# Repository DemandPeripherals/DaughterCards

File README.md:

# Daughter Cards
Eagle sources for schematic and board layout for all
of the Demand Peripherals daughter cards.

These drawings are released under the Creative Commons
Share-Alike 3.0 Unported license.  Please see LICENSE
for the text of the license.

The white directory contain the schematics and layout
for cards with a white silkscreen and which have either
3.5 or 1.575 inches between mounting holes.  The black
directory has the same, or newer, schematics for cards
which have 40 or 90 millimeter mounting hole spacing.

<p> &nbsp; </p>

# System Architecture
The following diagram shows the major components in the Demand
Peripherals system. Major components include: daughter cards,
the FPGA card, dpdaemon, and your application. (The FPGA card
supports eight daughter cards although this diagram shows only
three.)

<p> &nbsp; </p>

**Dpdaemon** is a set of user space device drivers implemented
as plug-in modules. The daemon provides an ASCII API over TCP.
The daemon also acts as a multiplexer for packets to and from
the FPGA. The real functionality of dpdaemon is in a set of
loadable shared object libraries (plug-ins). While intended to
support the FPGA-based peripherals in a Demand Peripherals FPGA
image, you may find that dpdaemon has several features you'll
find useful for your next Linux-to-hardware project:
    Command line tools to view and set plug-in parameters
    Simple publish/subscribe mechanism for sensor data
    All commands and data are printable ASCII over TCP
    Modular plug-ins (drivers) for easy development
    No dependencies (excluding libc)
    Event-driven and C means low CPU/memory footprint
    GPLv2 License.

**DPCore** is the FPGA part of the peripherals.  DPCore has the
timing and logic needed to drive the electronics on the daughter
cards. For example, the FPGA part of the dc2 peripheral does the
timing for the H-bridges that controls two DC motors. Logic in
the FPGA implements an internal address and data bus and each
peripheral has a set of 8-bit registers which configure the
peripheral. For example, the FPGA peripheral part of dc2 has an
8-bit register that sets the mode (brake, coast, forward, or
reverse) of each motor. Other registers in dc2 set the duty
cycle of the H-bridge FETs and configure the watchdog timer.

The defining feature of the Demand Peripherals approach is
that 32 of the FPGA pins are grouped into "slots" of exactly
4 pins each.  The slots are completely interchangeable and
any FPGA peripheral can attach to any slot.  The use of
ribbon cables makes it easy to attach any daughter card to
any slot.

**Daughter cards** contain the electronic components needed.
Daughter cards, called interface cards on the web site,might
contain the sensors, H-Bridge FETs, or the headers to connect
to servo motors. Each daughter card connects to the FPGA card
over an eight-wire IDC cable connected to one slot. The cable
has power lines and four pins from the FPGA.  Daughter card
designs are released under a Creative Commons license.

<p> &nbsp; </p>
The picture below shows a typical system with a single board
computer, an FPGA card, four daughter cards, and two dpdaemon
managed USB peripherals.

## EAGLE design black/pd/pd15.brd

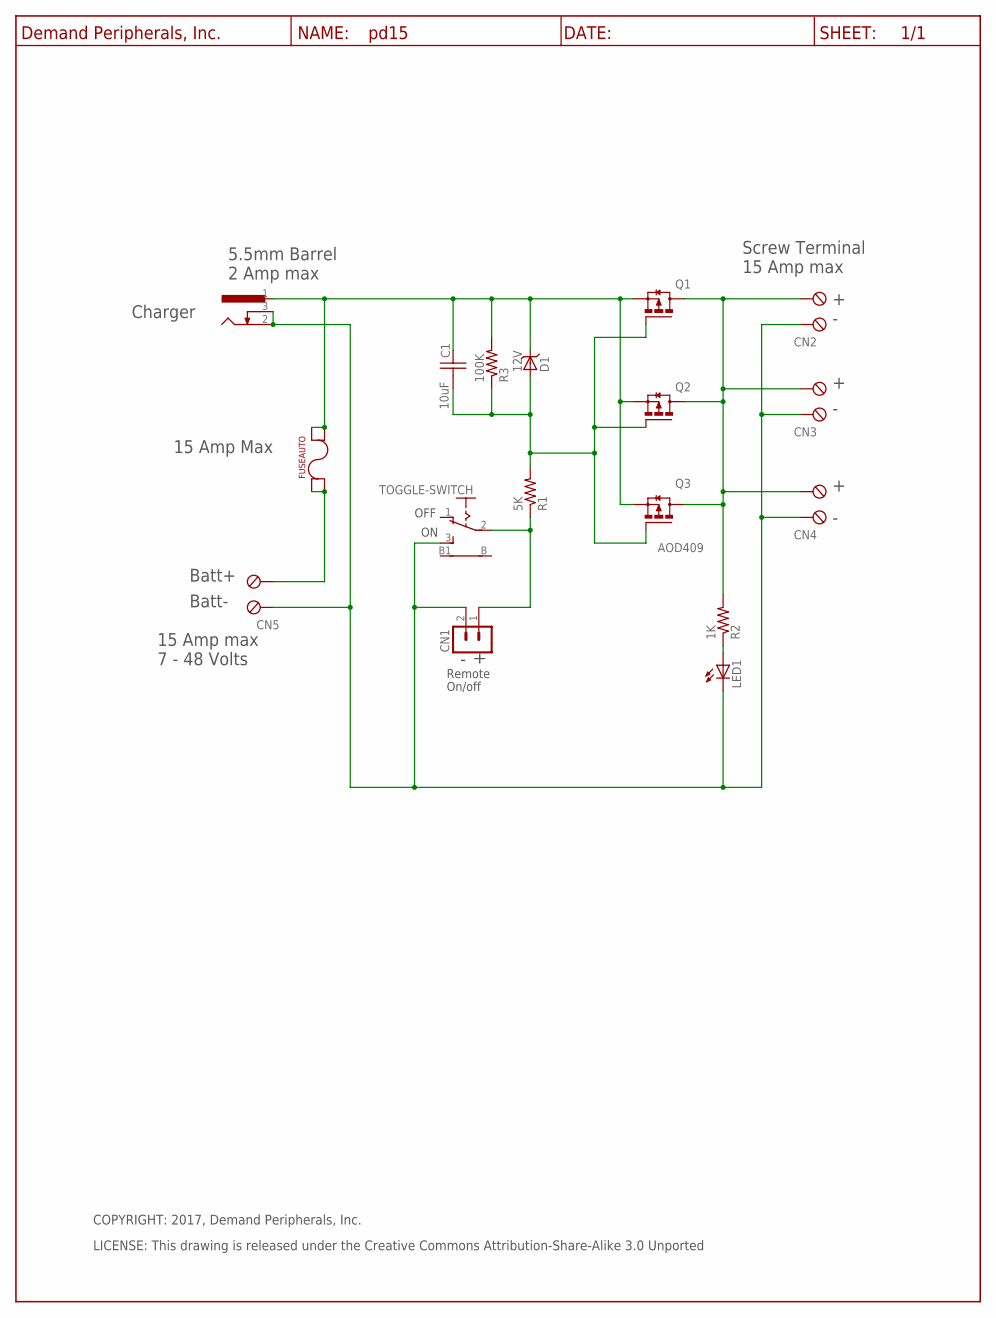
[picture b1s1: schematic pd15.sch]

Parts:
C1: 10uF; C0805
CN1: HDR-2X1-LCK; HDR-2X1
CN2, CN3, CN4, CN5: TBLK-5.08-X2
D1: 12V; SOD123
FUSE: FUSEAUTO; KS3557-10
J1: Barrel-5.5mm; DC-BARREL-JACK-55MM
LED1: LED-5MM-GRN; LED5MM
Q1, Q2: FET_DPAK_P; DPACK_TO-252
Q3: AOD409; DPACK_TO-252
R1: 5K; R0603
R2: 1K; R0603
R3: 100K; R0603
TOGGLE-SWITCH: B12EH; TOGGLE_SPDT_PC
U$1: DP_FRAME_P; LETTER_P

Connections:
BATT+: CN5.2 (KL1), FUSE.LS@1 (LS), FUSE.LS@2 (LS)
FUSE+: C1.1, D1.C, FUSE.RS@3 (RS), FUSE.RS@4 (RS), J1.1, Q1.3 (S), Q2.3 (S), Q3.3 (S), R3.2
GND: CN1.2 (1), CN2.1 (KL), CN3.1 (KL), CN4.1 (KL), CN5.1 (KL), J1.2, J1.3, LED1.C, TOGGLE-SWITCH.3 (S)
unnamed: LED1.A, R2.1
unnamed: C1.2, D1.A, Q1.1 (G), Q2.1 (G), Q3.1 (G), R1.2, R3.1
ON+: CN1.1 (2), R1.1, TOGGLE-SWITCH.2
V+: CN2.2 (KL1), CN3.2 (KL1), CN4.2 (KL1), Q1.4 (D), Q2.4 (D), Q3.4 (D), R2.2

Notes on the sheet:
Batt-
Batt+
Charger
OFF
Remote
On/off
15 Amp Max
7 - 48 Volts
15 Amp max
2 Amp max
5.5mm Barrel
Screw Terminal
COPYRIGHT: 2017, Demand Peripherals, Inc.
LICENSE: This drawing is released under the Creative Commons Attribution-Share-Alike 3.0 Unported

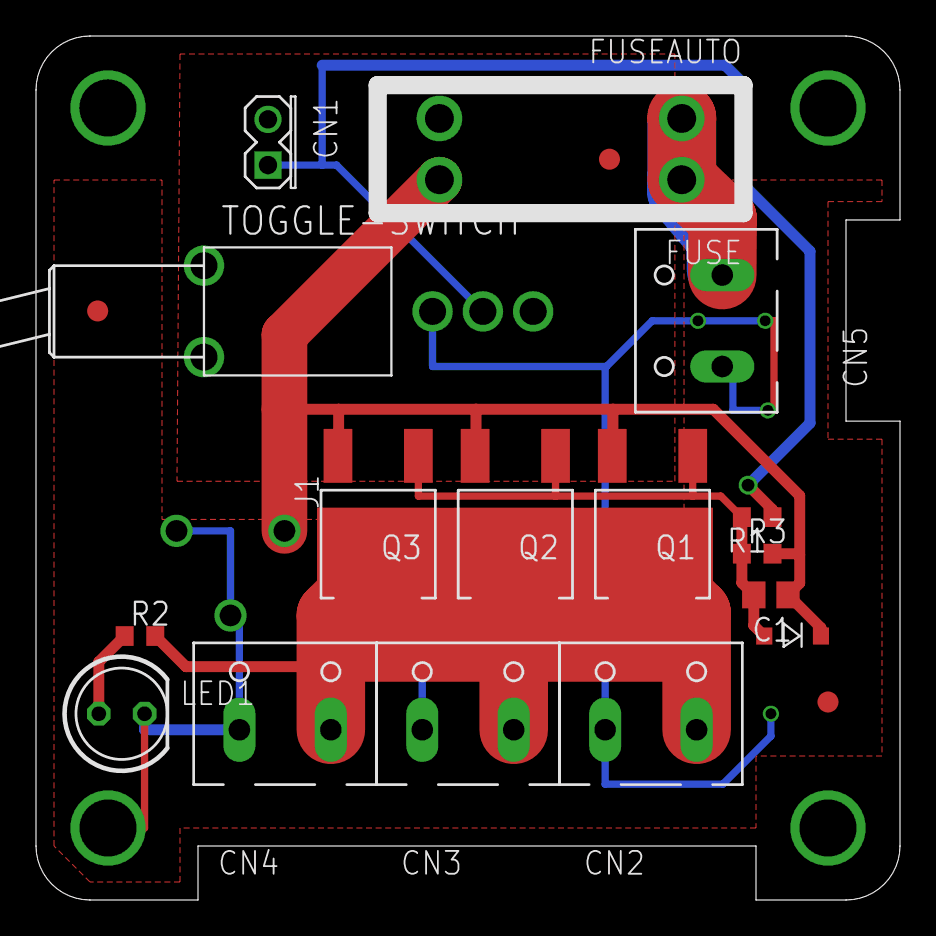
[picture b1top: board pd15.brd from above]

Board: 2 copper layers, 48.0 x 48.0 mm, 22 parts (1 on the bottom side), 7 nets.

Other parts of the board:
U$3, U$4, U$12: FIDUCIAL
U$8: DPI-2

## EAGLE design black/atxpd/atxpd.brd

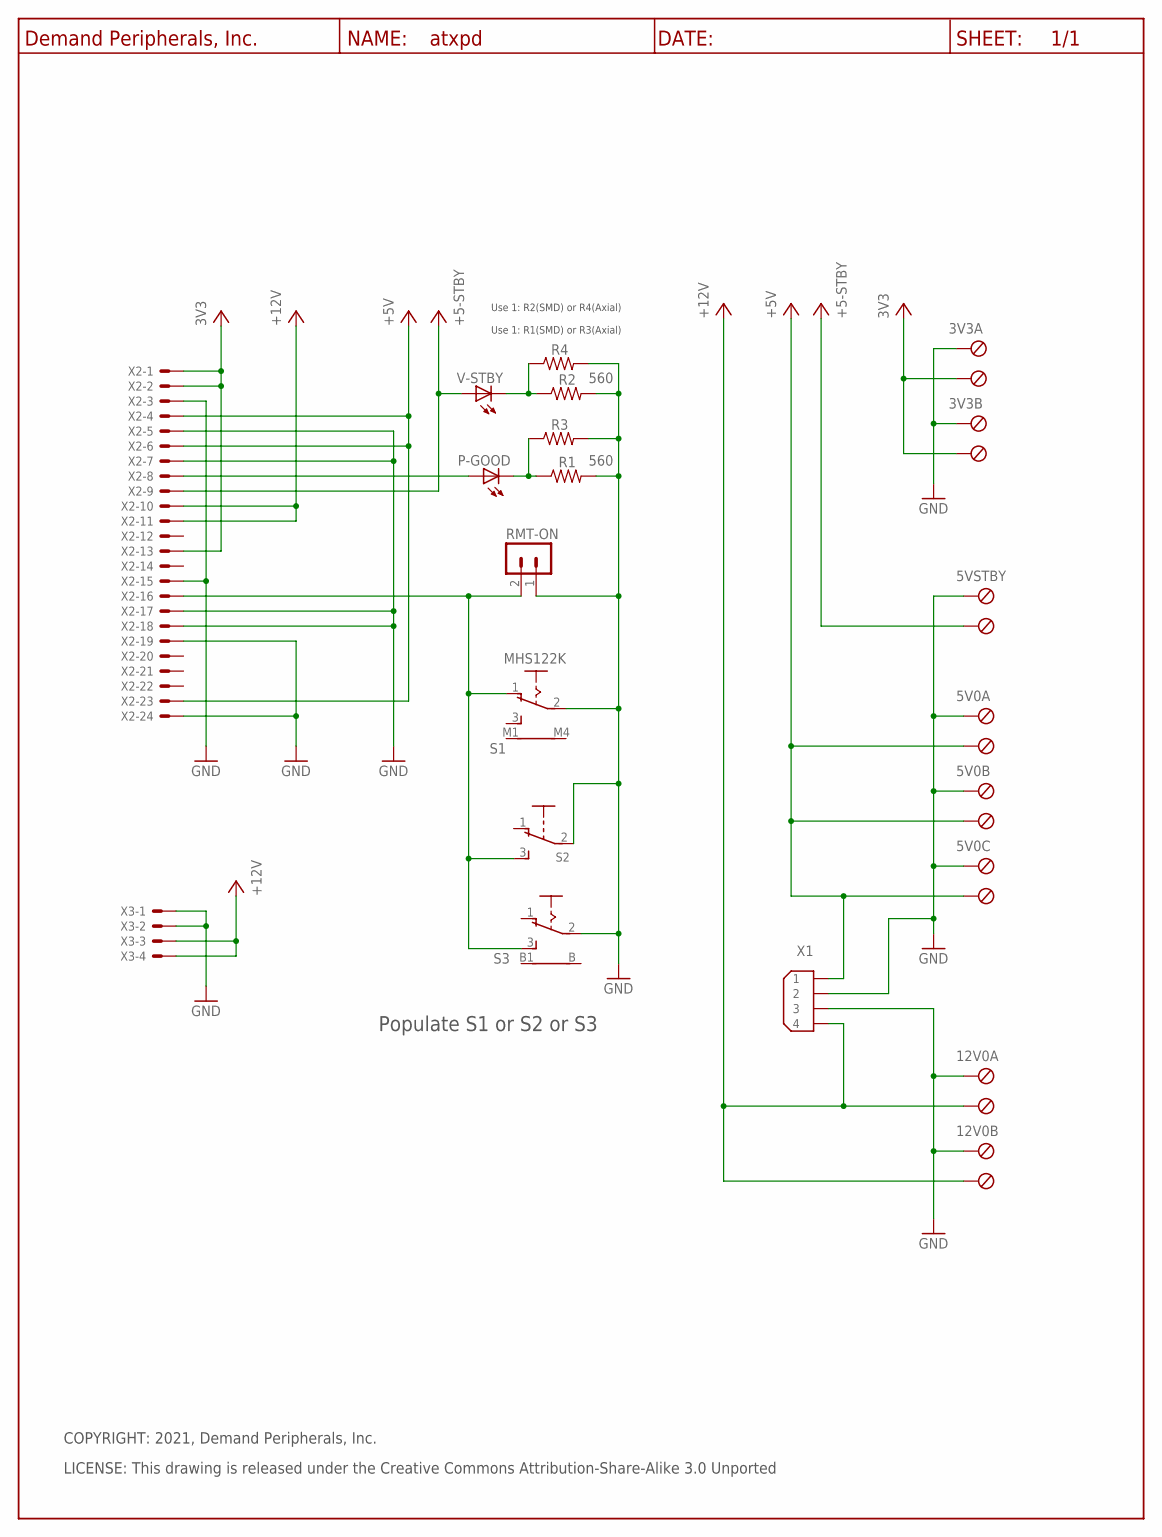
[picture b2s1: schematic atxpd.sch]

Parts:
3V3A, 3V3B, 5V0A, 5V0B, 5V0C, 5VSTBY, 12V0A, 12V0B: TBLK-5.08-X2
P-GOOD: 3mm_LED; LED5MM
R1, R2: 560; R0603
R3, R4: 560; R4TENTHS
RMT-ON: PinHdr254-2; HDR-2X1
S1: MHS122K
S2: TINYTOGGLE-SPDT-TH; SPDT-TENTHINCH
S3: Vert_SW(Option); TOGGLE_SPDT_PC
U$1: DP_FRAME_P; LETTER_P
V-STBY: 3mm_LED; LED5MM
X1: 9090-4V
X2: ATX_Std; 5566-24MOD
X3: ATX_Plus4; 5566-4MOD

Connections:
+3,3V: 3V3A.2 (KL1), 3V3B.2 (KL1), X2.1, X2.2, X2.13
+5V: 5V0A.2 (KL1), 5V0B.2 (KL1), 5V0C.2 (KL1), X1.1, X2.4, X2.6, X2.23
+5V/1: 5VSTBY.2 (KL1), V-STBY.A, X2.9
+5V/2: 12V0A.2 (KL1), 12V0B.2 (KL1), X1.4, X2.10, X2.11, X3.3, X3.4
GND: 3V3A.1 (KL), 3V3B.1 (KL), 5V0A.1 (KL), 5V0B.1 (KL), 5V0C.1 (KL), 5VSTBY.1 (KL), 12V0A.1 (KL), 12V0B.1 (KL), R1.2, R2.2, R3.2, R4.2, RMT-ON.1 (2), S1.2, S2.2, S3.2, X1.2, X1.3, X2.3, X2.5, X2.7, X2.15, X2.17, X2.18, X2.19, X2.24, X3.1, X3.2
unnamed: P-GOOD.A, X2.8
unnamed: P-GOOD.C, R1.1, R3.1
unnamed: R2.1, R4.1, V-STBY.C
unnamed: RMT-ON.2 (1), S1.1 (O), S2.3, S3.3 (S), X2.16

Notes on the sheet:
Use 1: R2(SMD) or R4(Axial)
Use 1: R1(SMD) or R3(Axial)
Populate S1 or S2 or S3
LICENSE: This drawing is released under the Creative Commons Attribution-Share-Alike 3.0 Unported
COPYRIGHT: 2021, Demand Peripherals, Inc.

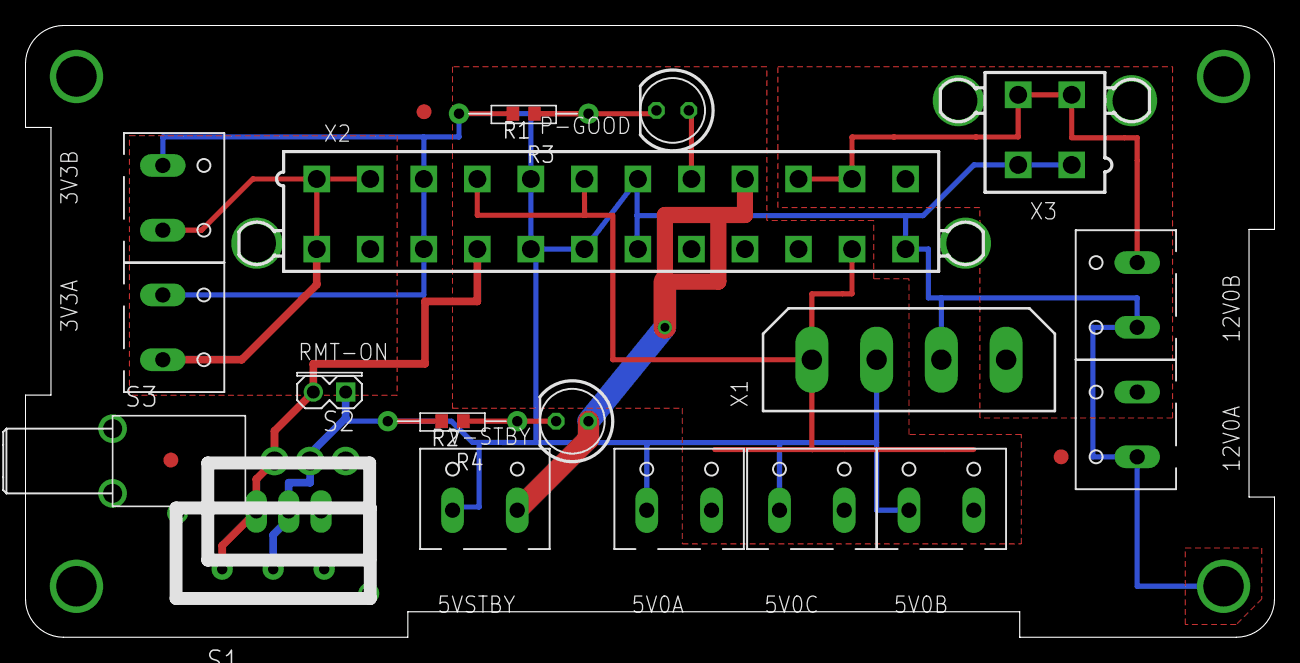
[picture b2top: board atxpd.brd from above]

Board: 2 copper layers, 98.0 x 48.0 mm, 27 parts (1 on the bottom side), 9 nets.

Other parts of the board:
U$9, U$10, U$11: FIDUCIAL
U$12, U$13: DPI-2

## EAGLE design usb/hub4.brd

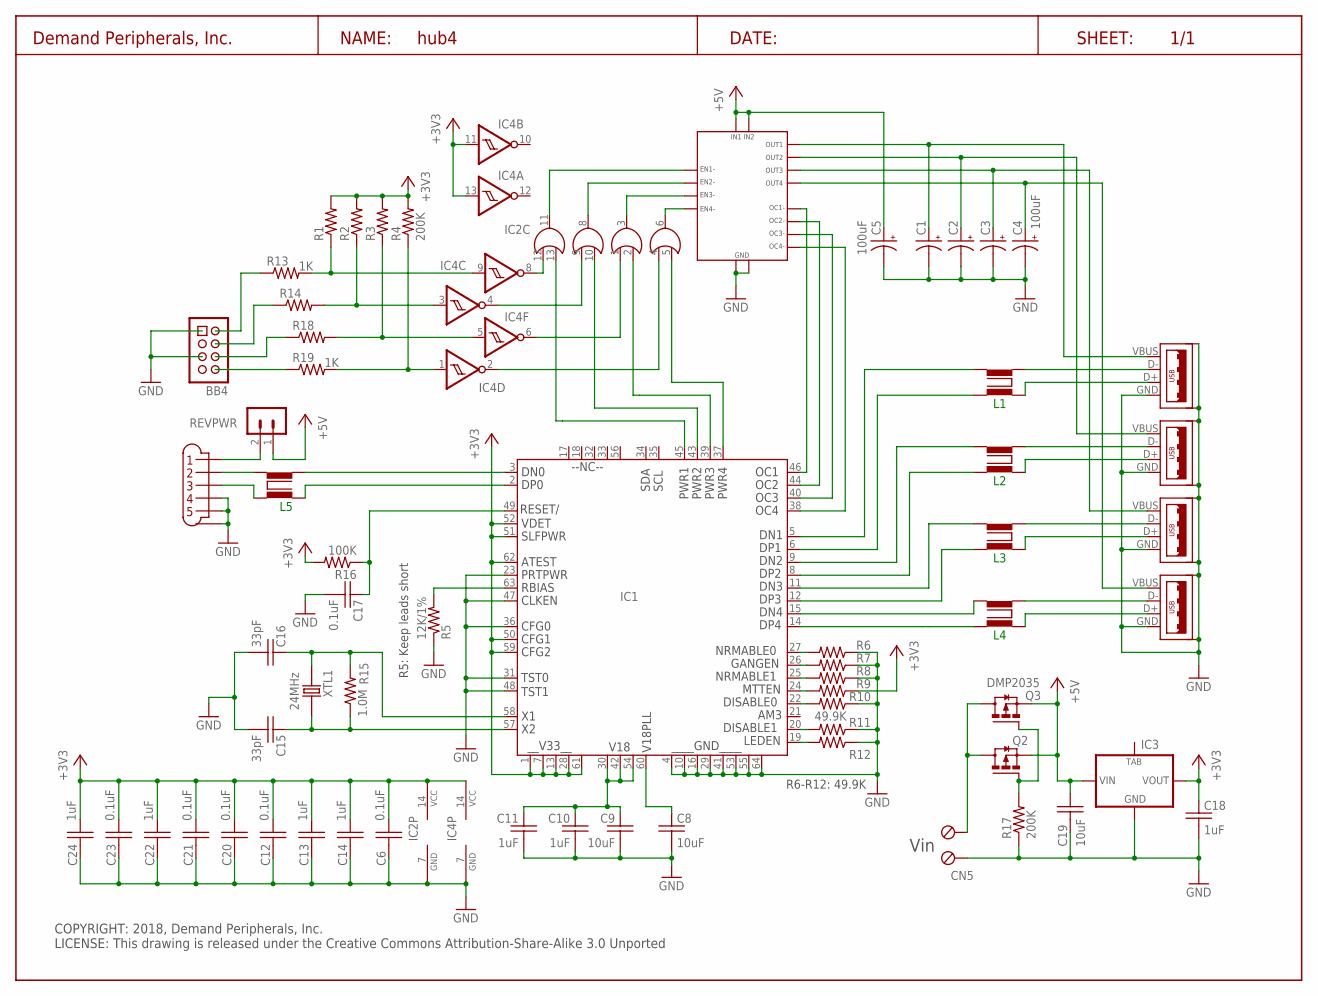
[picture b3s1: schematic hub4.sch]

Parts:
BB4: HDR-4X2-SHR; HDR-4X2
C1, C2, C3, C4, C5: 100uF; E3.5-8
C6, C12, C17, C20, C21, C23: 0.1uF; C0603
C8, C9, C19: 10uF; C0805
C10, C11, C13, C14, C18, C22, C24: 1uF; C0603
C15, C16: 33pF; C0603
CN1, CN2, CN3, CN4: USB_SINGLETHRU-HOLE; USB-A_1H
CN5: TBLK-5.08-X2
IC1: USB2504; TQFP64-10X10
IC2: 7432; SO14
IC3: LM1117A; SOT223
IC4: 7414; SO14
IC5: TPS2044; SO16
L1, L2, L3, L4, L5: ACM2012
Q2, Q3: DMP2035; SOT23
R1, R2, R3, R4, R17: 200K; R0603
R5: 12K/1%; R0603
R6, R7, R8, R9, R10, R11, R12: 49.9K; R0603
R13, R14, R18, R19: 1K; R0603
R15: 1.0M; R0603
R16: 100K; R0603
REVPWR: HDR-2X1-LCK; HDR-2X1
U$5: MINI-B; MINI-B-MOLEX
U$6: DP_FRAME_L; LETTER_L
XTL1: 24MHz; HC49S

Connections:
+3V3: C6.1, C12.1, C13.1, C14.1, C18.1, C20.1, C21.1, C22.1, C23.1, C24.1, IC1.1 (V33-0), IC1.7 (V33-1), IC1.13 (V33-2), IC1.28 (V33-3), IC1.50 (CFG1), IC1.51 (SLFPWR), IC1.52 (VDET), IC1.59 (CFG2), IC1.61 (V33-PLL), IC1.62 (ATEST), IC2.14 (VCC), IC3.2 (OUT), IC4.11 (I), IC4.13 (I), IC4.14 (VCC), R1.2, R2.2, R3.2, R4.2, R9.1, R16.2
+5V: C5.+, C19.1, IC3.3 (IN), IC5.2 (IN1), IC5.6 (IN2), Q2.2 (S), Q3.2 (S), REVPWR.1 (2)
GND: BB4.1, BB4.5, C1.-, C2.-, C3.-, C4.-, C5.-, C6.2, C8.2, C9.2, C10.2, C11.2, C12.2, C13.2, C14.2, C15.2, C16.2, C17.2, C18.2, C19.2, C20.2, C21.2, C22.2, C23.2, C24.2, CN1.GND (4), CN1.P$5 (5), CN1.P$6 (6), CN2.GND (4), CN2.P$5 (5), CN2.P$6 (6), CN3.GND (4), CN3.P$5 (5), CN3.P$6 (6), CN4.GND (4), CN4.P$5 (5), CN4.P$6 (6), CN5.1 (KL), IC1.4 (VSS0), IC1.10 (VSS1), IC1.16 (VSS2), IC1.23 (PTRPWR), IC1.29 (VSS3), IC1.31 (TST0), IC1.36 (CFG0), IC1.41 (VSS4), IC1.47 (CLKEN), IC1.48 (TST1), IC1.53 (VSS5), IC1.55 (VSS6), IC1.64 (VSS7), IC2.7 (GND), IC3.1 (GND), IC4.7 (GND), IC5.1 (GND1), IC5.5 (GND2), R5.1, R6.1, R7.1, R8.1, R10.1, R11.1, R12.1, R17.1, U$5.GND, U$5.P$4, U$5.P$5
unnamed: CN1.D- (2), L1.P$3 (3)
unnamed: CN1.D+ (3), L1.P$1 (1)
unnamed: IC1.14 (DP4), L4.P$4 (4)
unnamed: CN2.D- (2), L2.P$1 (1)
unnamed: CN2.D+ (3), L2.P$3 (3)
unnamed: CN3.D- (2), L3.P$3 (3)
unnamed: CN3.D+ (3), L3.P$1 (1)
unnamed: CN4.D- (2), L4.P$1 (1)
unnamed: CN4.D+ (3), L4.P$3 (3)
unnamed: IC1.15 (DN4), L4.P$2 (2)
unnamed: IC1.12 (DP3), L3.P$2 (2)
unnamed: IC1.11 (DN3), L3.P$4 (4)
unnamed: REVPWR.2 (1), U$5.P$1
unnamed: IC1.8 (DP2), L2.P$4 (4)
unnamed: IC1.9 (DN2), L2.P$2 (2)
unnamed: IC1.6 (DP1), L1.P$2 (2)
unnamed: IC1.5 (DN1), L1.P$4 (4)
unnamed: L5.P$3 (3), U$5.P$3
unnamed: L5.P$1 (1), U$5.P$2
unnamed: IC2.12 (I0), IC4.8 (O)
unnamed: IC2.9 (I0), IC4.4 (O)
unnamed: IC2.1 (I0), IC4.6 (O)
unnamed: IC1.46 (OC1), IC5.16 (OC1-)
unnamed: IC1.44 (OC2), IC5.13 (OC2-)
unnamed: IC1.40 (OC3), IC5.12 (OC3-)
unnamed: IC1.38 (OC4), IC5.9 (OC4-)
unnamed: IC2.4 (I0), IC4.2 (O)
unnamed: IC1.45 (PWR1), IC2.13 (I1)
unnamed: IC1.43 (PWR2), IC2.10 (I1)
unnamed: IC1.39 (PWR3), IC2.2 (I1)
unnamed: BB4.2, R13.1
unnamed: IC1.37 (PWR4), IC2.5 (I1)
unnamed: IC2.6 (O), IC5.8 (EN4-)
unnamed: IC2.3 (O), IC5.7 (EN3-)
unnamed: IC2.8 (O), IC5.4 (EN2-)
unnamed: IC2.11 (O), IC5.3 (EN1-)
unnamed: IC4.9 (I), R1.1, R13.2
unnamed: C16.1, IC1.58 (X1), R15.2, XTL1.P$2 (2)
unnamed: C1.+, CN1.VBUS (1), IC5.15 (OUT1)
unnamed: C9.1, C10.1, C11.1, IC1.30 (V18-0), IC1.42 (V18-1), IC1.54 (V18-3)
unnamed: CN5.2 (KL1), Q2.3 (D), Q3.3 (D)
unnamed: Q2.1 (G), Q3.1 (G), R17.2
unnamed: IC1.63 (RBIAS), R5.2
unnamed: IC4.3 (I), R2.1, R14.2
unnamed: IC4.5 (I), R3.1, R18.2
unnamed: C8.1, IC1.60 (V18PLL)
unnamed: IC4.1 (I), R4.1, R19.2
unnamed: C15.1, IC1.57 (X2), R15.1, XTL1.P$1 (1)
unnamed: IC1.27 (GR1), R6.2
unnamed: C17.1, IC1.49 (RESET), R16.1
unnamed: IC1.26 (AM1), R7.2
unnamed: BB4.4, R14.1
unnamed: IC1.25 (GR2), R8.2
unnamed: IC1.24 (AM2), R9.2
unnamed: BB4.6, R18.1
unnamed: BB4.8, R19.1
unnamed: IC1.22 (GR3), R10.2
unnamed: IC1.20 (GR4), R11.2
unnamed: IC1.19 (AM4), R12.2
unnamed: IC1.3 (DN0), L5.P$2 (2)
unnamed: IC1.2 (DP0), L5.P$4 (4)
unnamed: C2.+, CN2.VBUS (1), IC5.14 (OUT2)
unnamed: C3.+, CN3.VBUS (1), IC5.11 (OUT3)
unnamed: C4.+, CN4.VBUS (1), IC5.10 (OUT4)

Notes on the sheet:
Vin
R5: Keep leads short
R6-R12: 49.9K
COPYRIGHT: 2018, Demand Peripherals, Inc. LICENSE: This drawing is released under the Creative Commons Attribution-Share-Alike 3.0 Unported

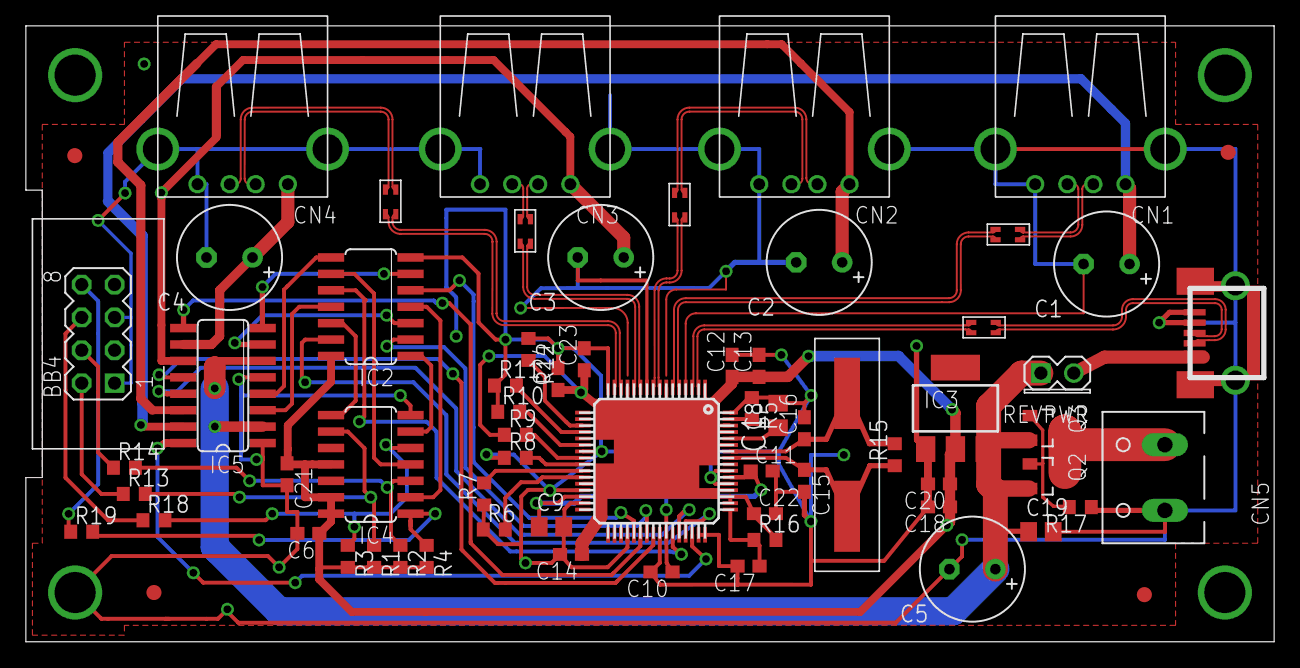
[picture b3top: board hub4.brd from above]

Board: 2 copper layers, 96.5 x 47.6 mm, 69 parts (1 on the bottom side), 67 nets.

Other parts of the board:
U$1, U$2, U$3, U$4: FIDUCIAL
U$8: DPI-2

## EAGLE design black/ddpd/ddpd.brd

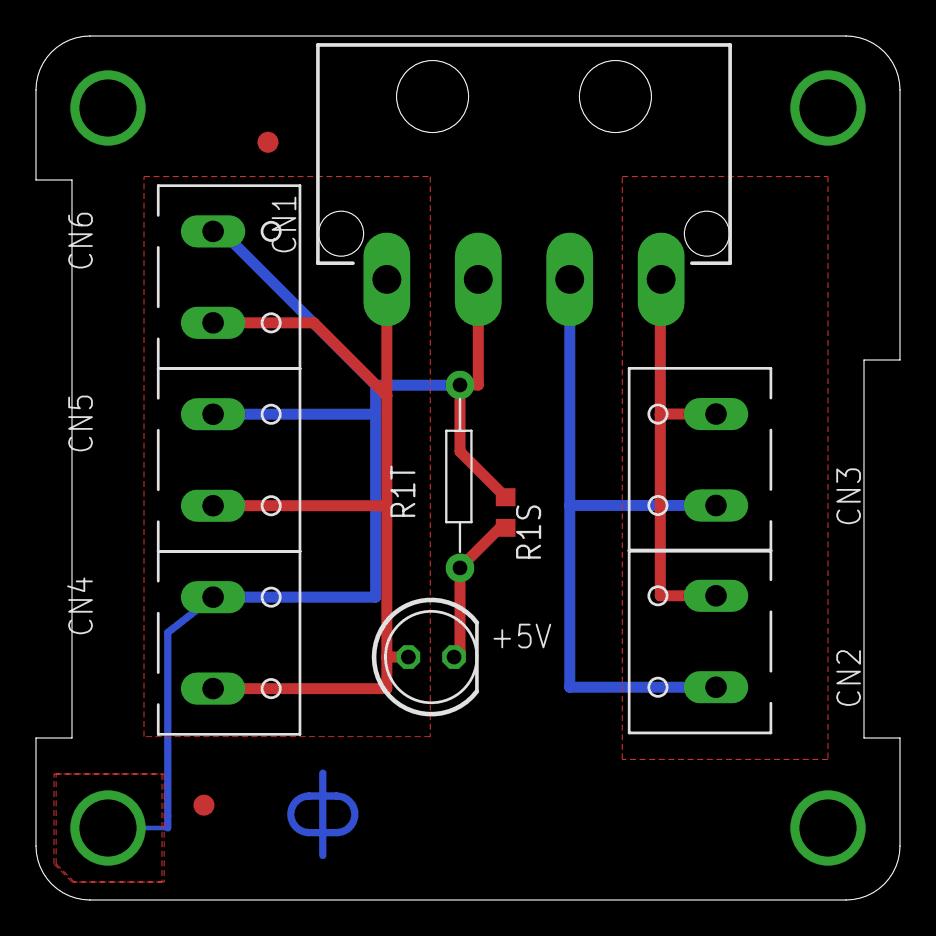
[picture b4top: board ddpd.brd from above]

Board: 2 copper layers, 48.0 x 48.0 mm, 13 parts (1 on the bottom side), 5 nets.

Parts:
+5V: LED-5MM-GRN; LED5MM
CN1: 9090-4V; 9090-4R
CN2, CN3, CN4, CN5, CN6: TBLK-5.08-X2
R1S: 560; R0603
R1T: 560; R4TENTHS
U$1: DPI-1
U$2, U$3: FIDUCIAL
U$4: DP_FRAME_P; LETTER_P

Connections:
+5V: +5V.A, CN1.1, CN4.2, CN5.2, CN6.2
+5V/2: CN1.4, CN2.2, CN3.2
GND: CN1.2, CN4.1, CN5.1, CN6.1, R1S.1, R1T.2
GND1: CN1.3, CN2.1, CN3.1
unnamed: +5V.C, R1S.2, R1T.1

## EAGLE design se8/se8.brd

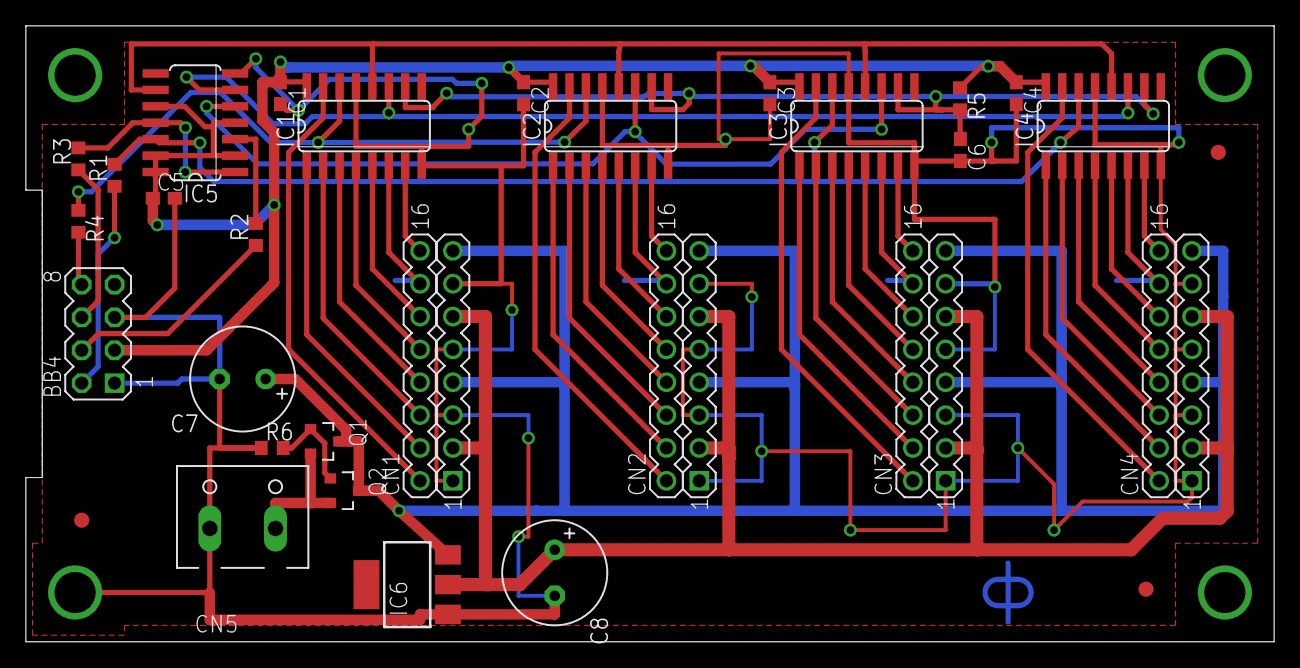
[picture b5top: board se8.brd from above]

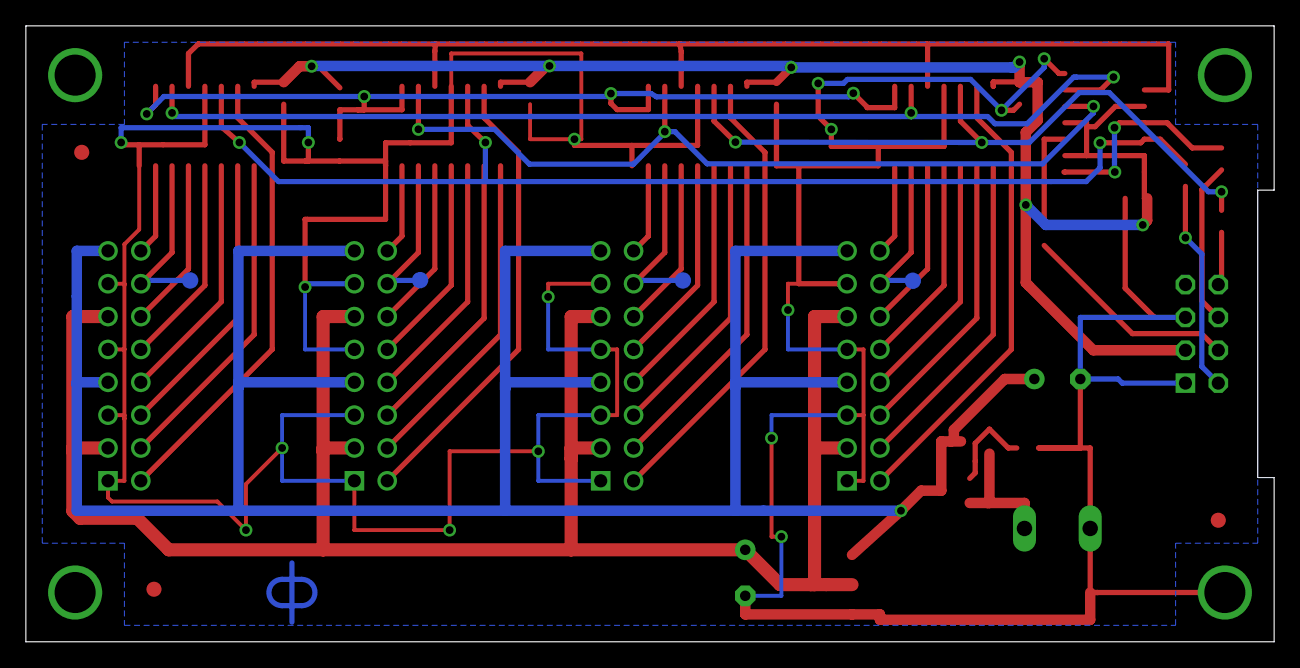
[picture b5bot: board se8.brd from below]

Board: 2 copper layers, 96.5 x 47.6 mm, 39 parts (5 on the bottom side), 50 nets.

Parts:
BB4: BB4 Header; HDR-4X2
C1, C2, C3, C4, C5, C6: 0.1uF; C0603
C7, C8: 100uF; E3.5-8
CN1, CN2, CN3, CN4: HDR-8X2-SHR; HDR-8X2
CN5: TBLK-5.08-X2
E$1, E$2, E$3, E$4: TEST-POINT
E$25: P_FRAME
IC1, IC2, IC3, IC4: 74HC595; SO16
IC5: 74HC74; SO14
IC6: NCP1117A; SOT223
Q1, Q2: DMP2035; SOT23
R1, R2, R3, R4: 100; R0603
R5: 330; R0603
R6: 100K; R0603
U$1: P_FRAME
U$2: DP_FRAME_P; P_FRAME
U$4, U$5, U$6: FIDUCIAL
U$7: DPI-1

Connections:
+3V3: BB4.3, C1.1, C2.1, C3.1, C4.1, C5.1, IC1.16, IC2.16, IC3.16, IC4.16, IC5.2, IC5.4, IC5.10, IC5.13, IC5.14, R5.1
GND: BB4.1, BB4.5, C1.2, C2.2, C3.2, C4.2, C5.2, C6.2, C7.-, C8.-, CN1.1, CN1.5, CN1.9, CN1.13, CN2.1, CN2.5, CN2.9, CN2.13, CN3.1, CN3.5, CN3.9, CN3.13, CN4.1, CN4.5, CN4.9, CN4.13, CN5.1, IC1.8, IC1.13, IC2.8, IC2.13, IC3.8, IC3.13, IC4.8, IC4.13, IC5.7, IC6.1, R6.1
unnamed: BB4.8, R4.2
unnamed: CN4.2, IC4.15
unnamed: IC1.12, IC2.12, IC3.12, IC4.12, IC5.9
unnamed: IC2.11, IC3.11, IC5.5
unnamed: CN4.4, IC4.1
unnamed: CN4.6, IC4.2
unnamed: CN4.8, IC4.3
unnamed: CN4.10, IC4.4
unnamed: CN4.12, IC4.5
unnamed: CN4.14, IC4.6
unnamed: CN4.16, IC4.7
unnamed: CN3.2, IC3.15
unnamed: CN3.4, IC3.1
unnamed: CN3.6, IC3.2
unnamed: CN3.8, IC3.3
unnamed: CN3.10, IC3.4
unnamed: CN3.12, IC3.5
unnamed: CN3.14, IC3.6
unnamed: CN3.16, IC3.7
unnamed: CN2.2, IC2.15
unnamed: CN2.4, IC2.1
unnamed: CN2.6, IC2.2
unnamed: CN2.8, IC2.3
unnamed: CN2.10, IC2.4
unnamed: CN2.12, IC2.5
unnamed: BB4.2, R1.1
unnamed: CN2.14, IC2.6
unnamed: CN2.16, IC2.7
unnamed: IC5.3, R2.2
unnamed: IC3.14, IC4.14, IC5.12, R1.2
unnamed: IC5.1, IC5.11, R3.2
unnamed: IC1.14, IC2.14, R4.1
unnamed: BB4.6, R3.1
unnamed: IC1.11, IC4.11, IC5.6
unnamed: BB4.4, R2.1
unnamed: CN1.2, IC1.15
unnamed: CN1.4, IC1.1
unnamed: CN1.6, IC1.2
unnamed: CN1.8, IC1.3
unnamed: C6.1, IC1.10, IC2.10, IC3.10, IC4.10, R5.2
unnamed: CN1.10, IC1.4
unnamed: CN1.12, IC1.5
unnamed: CN1.14, IC1.6
unnamed: CN1.16, IC1.7
unnamed: C7.+, CN1.7, CN1.15, CN2.7, CN2.15, CN3.7, CN3.15, CN4.7, CN4.15, IC6.3, Q1.3, Q2.3
unnamed: CN5.2, Q1.2, Q2.2
unnamed: Q1.1, Q2.1, R6.2
unnamed: C8.+, CN1.3, CN1.11, CN2.3, CN2.11, CN3.3, CN3.11, CN4.3, CN4.11, IC6.2

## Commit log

2020-05-23 Initial check-in
2020-05-23 switched from an HTML CCv3 to a text one
2020-05-23 Changed from an HTML version of CCv3 to a text one.
2021-01-28 Created 'white' for the old white boards with imperial spacking and 'black' for the new black boards with metric spacing.
2021-01-30 Added images to the white board design files
2021-02-01 Converted the ATXPD and DDPD cards to metric spacing. Fixed a bug the ATXPD schematic.
2021-02-02 Moved dp15 to metric spacing. Removed the paddle switch from the schematic.

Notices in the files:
black/atxpd/atxpd.brd:
(C) 2021, Demand Peripherals, Inc.
se8/se8.brd:
(C) 2017, Demand Peripherals, Inc.
usb/hub4.brd:
(C) 2018, Demand Peripherals, Inc.
